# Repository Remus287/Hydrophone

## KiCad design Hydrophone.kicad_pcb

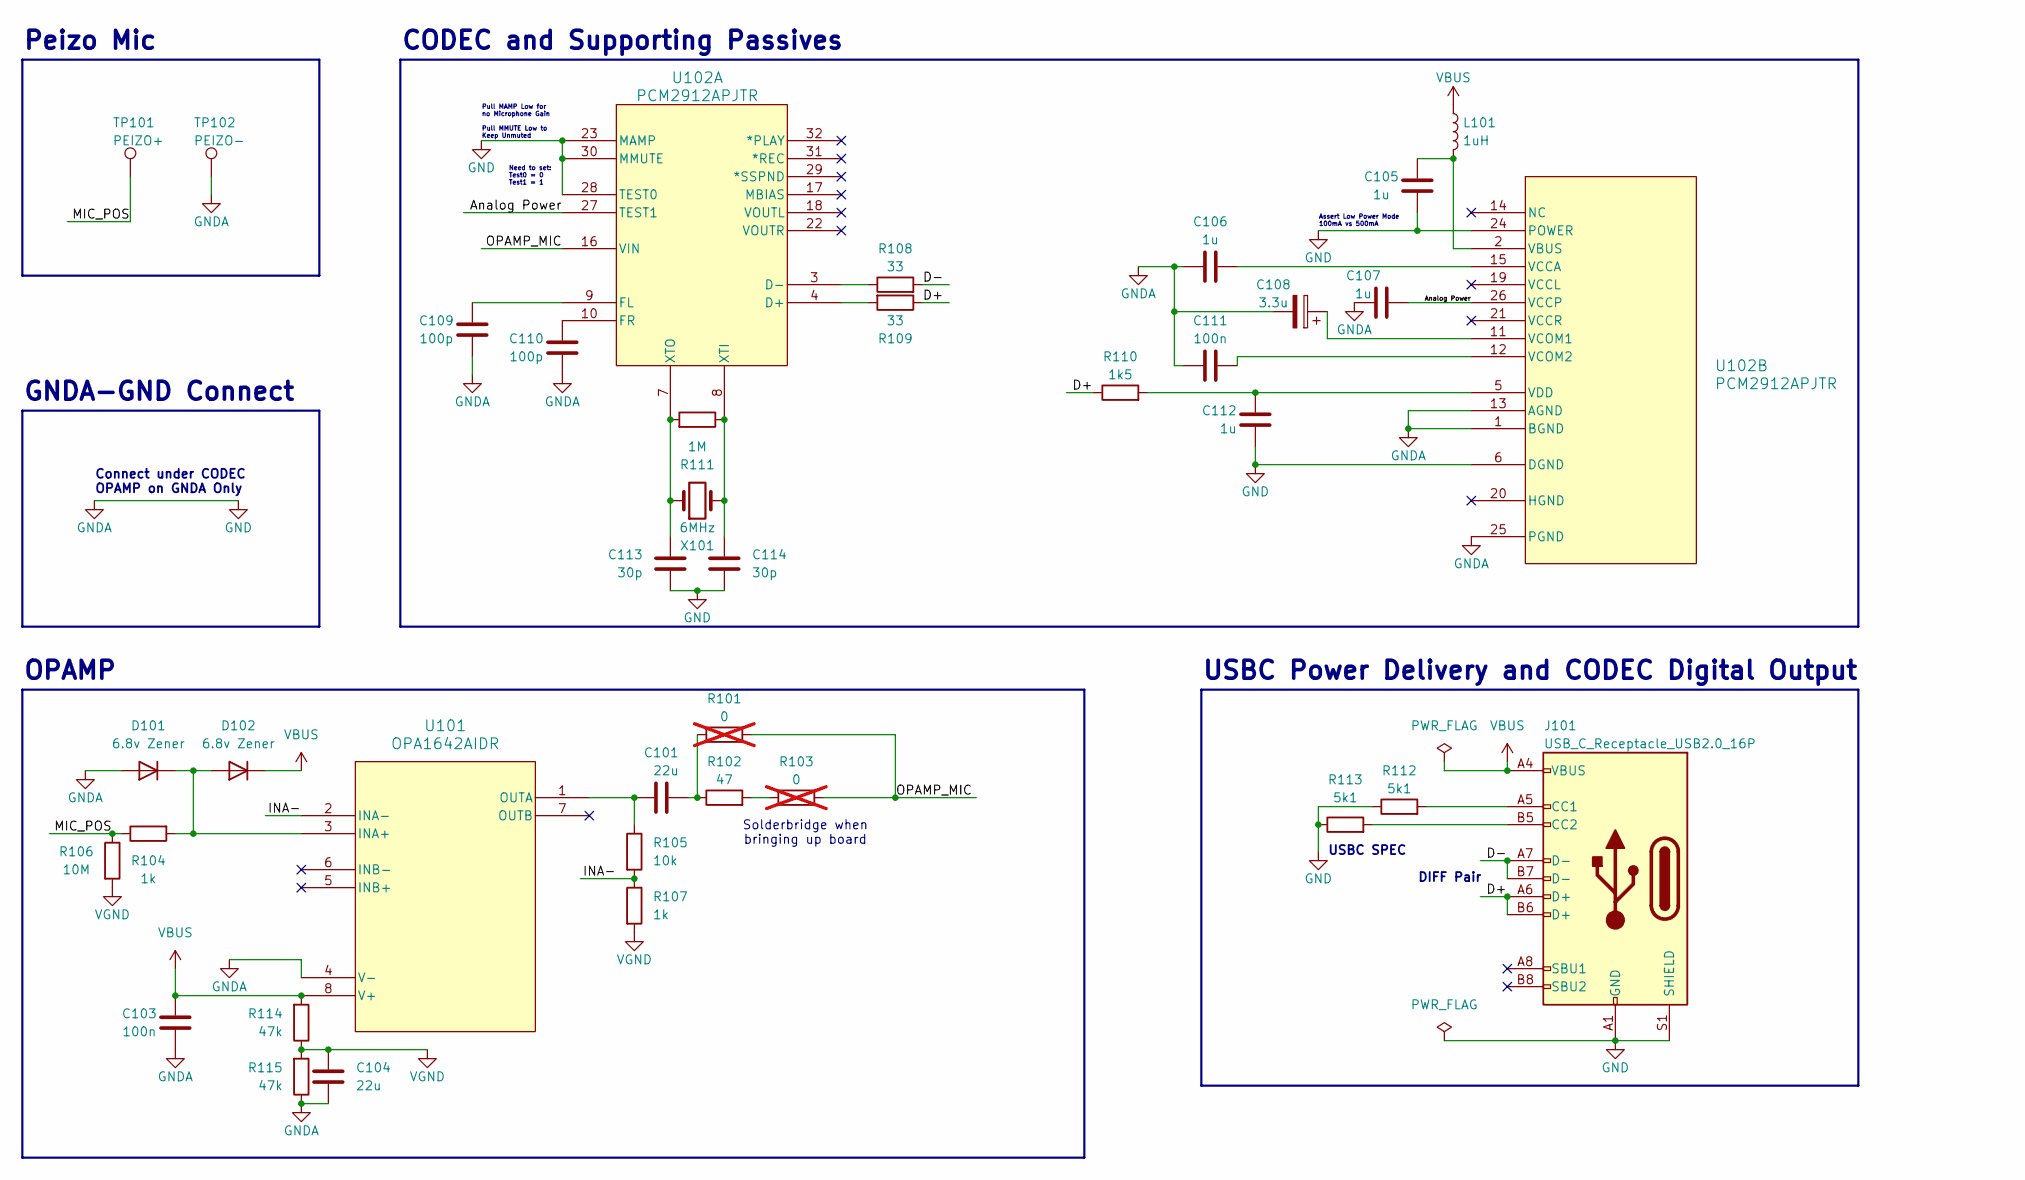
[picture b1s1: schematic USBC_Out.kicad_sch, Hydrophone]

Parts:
C101, C104: 22u; C_0805_2012Metric; Part Number CL21A226MAQNNNE; JLCPCB Part# C45783
C103, C111: 100n; C_0402_1005Metric; Part Number CL05B104KO5NNNC; JLCPCB Part# C1525
C105, C106, C107, C112: 1u; C_0402_1005Metric; Part Number CL05A105KA5NQNC; JLCPCB Part# C52923
C108: 3.3u; CP_EIA-3216-18_Kemet-A; Part Number TAJA335K016RNJ; JLCPCB Part# C7184
C109, C110: 100p; C_0402_1005Metric; Part Number 0402CG101J500NT; JLCPCB Part# C1546
C113, C114: 30p; C_0402_1005Metric; Part Number 0402CG300J500NT; JLCPCB Part# C1570
D101, D102: 6.8v Zener; D_SOD-123; Part Number BZT52C6V8; JLCPCB Part# C2120
J101: USB_C_Receptacle_USB2.0_16P; USB_C_Receptacle_G-Switch_GT-USB-7025; Part Number GT-USB-7025; JLCPCB Part# C963213
L101: 1uH; L_1210_3225Metric; Part Number NLV32T-1R0J-PF; JLCPCB Part# C22202
R101, R103: 0; R_0603_1608Metric; not fitted
R102: 47; R_0805_2012Metric; Part Number 1206W4F1002T5E; JLCPCB Part# C17902
R104, R107: 1k; C_0402_1005Metric; Part Number 0402WGF1001TCE; JLCPCB Part# C11702
R105: 10k; R_1206_3216Metric; Part Number 1206W4F1002T5E; JLCPCB Part# C17902
R106: 10M; R_0402_1005Metric; Part Number 0402WGF1005TCE; JLCPCB Part# C26082
R108, R109: 33; R_0402_1005Metric; Part Number 0402WGF330JTCE; JLCPCB Part# C25105
R110: 1k5; R_0402_1005Metric; Part Number 0402WGJ0152TCE; JLCPCB Part# C25930
R111: 1M; R_0402_1005Metric; Part Number 0402WGF1004TCE; JLCPCB Part# C26083
R112, R113: 5k1; R_0402_1005Metric; Part Number 0402WGF5101TCE; JLCPCB Part# C25905
R114, R115: 47k; R_0402_1005Metric; Part Number 0402WGF4702TCE; JLCPCB Part# C25792
TP101: PEIZO+; TestPoint_Pad_D1.0mm; Part Number ---
TP102: PEIZO-; TestPoint_Pad_D1.0mm; Part Number ---
U101: OPA1642AIDR; D8; Part Number OPA1642AIDR; JLCPCB Part# C67640
U102: PCM2912APJTR; PJT32; Part Number PCM2912APJTR; JLCPCB Part# C475497
X101: 6MHz; Crystal_SMD_HC49-SD; Part Number H6OEL89CSC-SUGYLC-6M; JLCPCB Part# C7528811

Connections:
/USBC_Out/Analog Power: C107.1, U102.26 (VCCP), U102.27 (TEST1)
/USBC_Out/D+: J101.A6 (D+), J101.B6 (D+), R109.1, R110.1
/USBC_Out/D-: J101.A7 (D-), J101.B7 (D-), R108.2
/USBC_Out/INA-: R105.2, R107.1, U101.2 (INA-)
/USBC_Out/MIC_POS: R104.1, R106.1, TP101.1
/USBC_Out/OPAMP_MIC: R101.2, R103.2, U102.16 (VIN)
GND: C103.2, C104.2, C105.2, C106.2, C107.2, C108.2, C109.2, C110.2, C111.2, C112.1, C113.2, C114.2, D101.2 (A), J101.A1 (GND), J101.A12 (GND), J101.B1 (GND), J101.B12 (GND), J101.S1 (SHIELD), R112.1, R113.1, R115.1, TP102.1, U101.4 (V-), U102.1 (BGND), U102.6 (DGND), U102.13 (AGND), U102.23 (MAMP), U102.24 (POWER), U102.25 (PGND), U102.28 (TEST0), U102.30 (MMUTE)
unnamed: C101.1, R101.1, R102.1
unnamed: D101.1 (K), D102.2 (A), R104.2, U101.3 (INA+)
unnamed: J101.A5 (CC1), R112.2
unnamed: J101.B5 (CC2), R113.2
unnamed: R102.2, R103.1
unnamed: C101.2, R105.1, U101.1 (OUTA)
unnamed: R109.2, U102.4 (D+)
unnamed: R108.1, U102.3 (D-)
unnamed: C109.1, U102.9 (FL)
unnamed: C110.1, U102.10 (FR)
unnamed: C114.1, R111.1, U102.8 (XTI), X101.2
unnamed: C113.1, R111.2, U102.7 (XTO), X101.1
unnamed: C105.1, L101.2, U102.2 (VBUS)
unnamed: C106.1, U102.15 (VCCA)
unnamed: C108.1, U102.11 (VCOM1)
unnamed: C111.1, U102.12 (VCOM2)
unnamed: C112.2, R110.2, U102.5 (VDD)
VBUS: C103.1, D102.1 (K), J101.A4 (VBUS), J101.A9 (VBUS), J101.B4 (VBUS), J101.B9 (VBUS), L101.1, R114.2, U101.8 (V+)
VGND: C104.1, R106.2, R107.2, R114.1, R115.2

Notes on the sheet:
DIFF Pair
Need to set: Test0 = 0 Test1 = 1
USBC Power Delivery and CODEC Digital Output
Assert Low Power Mode 100mA vs 500mA
USBC SPEC
CODEC and Supporting Passives
Connect under CODEC OPAMP on GNDA Only
Solderbridge when bringing up board
Peizo Mic
Pull MAMP Low for no Microphone Gain Pull MMUTE Low to Keep Unmuted
OPAMP
GNDA-GND Connect

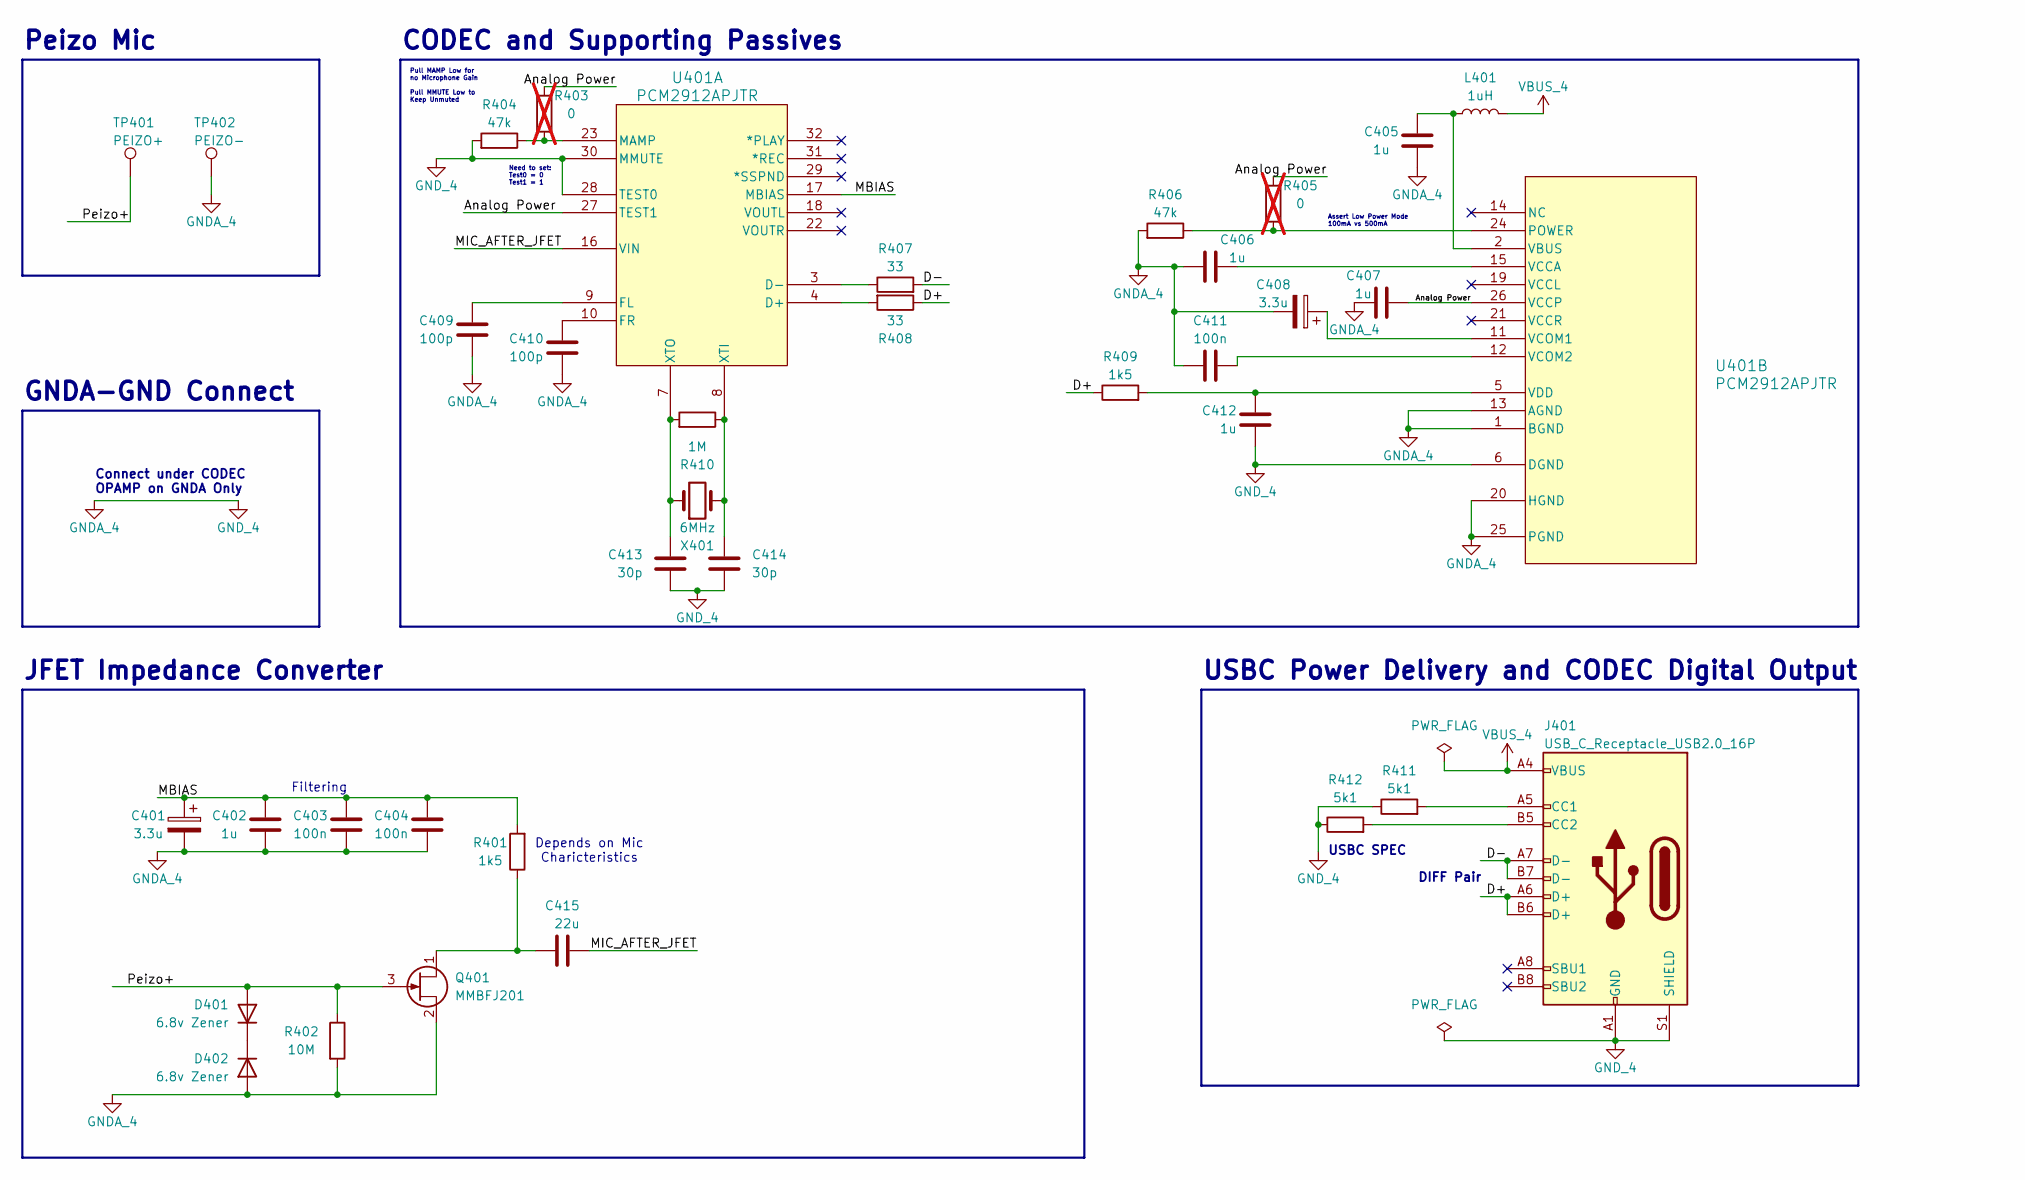
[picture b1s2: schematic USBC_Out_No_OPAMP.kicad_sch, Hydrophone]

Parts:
C401, C408: 3.3u; CP_EIA-3216-18_Kemet-A; Part Number TAJA335K016RNJ; JLCPCB Part# C7184
C402, C405, C406, C407, C412: 1u; C_0402_1005Metric; Part Number CL05A105KA5NQNC; JLCPCB Part# C52923
C403, C404, C411: 100n; C_0402_1005Metric; Part Number CL05B104KO5NNNC; JLCPCB Part# C1525
C409, C410: 100p; C_0402_1005Metric; Part Number 0402CG101J500NT; JLCPCB Part# C1546
C413, C414: 30p; C_0402_1005Metric; Part Number 0402CG300J500NT; JLCPCB Part# C1570
C415: 22u; C_0805_2012Metric; Part Number CL21A226MAQNNNE; JLCPCB Part# C45783
D401, D402: 6.8v Zener; D_SOD-123; Part Number BZT52C6V8; JLCPCB Part# C2120
J401: USB_C_Receptacle_USB2.0_16P; USB_C_Receptacle_G-Switch_GT-USB-7025; Part Number GT-USB-7025; JLCPCB Part# C963213
L401: 1uH; L_1210_3225Metric; Part Number NLV32T-1R0J-PF; JLCPCB Part# C22202
Q401: MMBFJ201; SOT-23; Part Number MMBFJ201; JLCPCB Part# C891687
R401, R409: 1k5; R_0402_1005Metric; Part Number 0402WGJ0152TCE; JLCPCB Part# C25930
R402: 10M; R_0402_1005Metric; Part Number 0402WGF1005TCE; JLCPCB Part# C26082
R403, R405: 0; R_0603_1608Metric; not fitted
R404, R406: 47k; R_0402_1005Metric; Part Number 0402WGF4702TCE; JLCPCB Part# C25792
R407, R408: 33; R_0402_1005Metric; Part Number 0402WGF330JTCE; JLCPCB Part# C25105
R410: 1M; R_0402_1005Metric; Part Number 0402WGF1004TCE; JLCPCB Part# C26083
R411, R412: 5k1; R_0402_1005Metric; Part Number 0402WGF5101TCE; JLCPCB Part# C25905
TP401: PEIZO+; TestPoint_Pad_D1.0mm; Part Number ---
TP402: PEIZO-; TestPoint_Pad_D1.0mm; Part Number ---
U401: PCM2912APJTR; PJT32; Part Number PCM2912APJTR; JLCPCB Part# C475497
X401: 6MHz; Crystal_SMD_HC49-SD; Part Number H6OEL89CSC-SUGYLC-6M; JLCPCB Part# C7528811

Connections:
/USBC_Out_No_OPAMP/Analog Power: C407.1, R403.2, R405.2, U401.26 (VCCP), U401.27 (TEST1)
/USBC_Out_No_OPAMP/D+: J401.A6 (D+), J401.B6 (D+), R408.1, R409.1
/USBC_Out_No_OPAMP/D-: J401.A7 (D-), J401.B7 (D-), R407.2
/USBC_Out_No_OPAMP/MBIAS: C401.1, C402.2, C403.2, C404.2, R401.2, U401.17 (MBIAS)
/USBC_Out_No_OPAMP/MIC_AFTER_JFET: C415.1, U401.16 (VIN)
/USBC_Out_No_OPAMP/Peizo+: D401.2 (A), Q401.3 (G), R402.1, TP401.1
GNDA_4: C401.2, C402.1, C403.1, C404.1, C405.2, C406.2, C407.2, C408.2, C409.2, C410.2, C411.2, C412.1, C413.2, C414.2, D402.2 (A), J401.A1 (GND), J401.A12 (GND), J401.B1 (GND), J401.B12 (GND), J401.S1 (SHIELD), Q401.2 (S), R402.2, R404.2, R406.2, R411.1, R412.1, TP402.1, U401.1 (BGND), U401.6 (DGND), U401.13 (AGND), U401.20 (HGND), U401.25 (PGND), U401.28 (TEST0), U401.30 (MMUTE)
unnamed: D401.1 (K), D402.1 (K)
unnamed: J401.A5 (CC1), R411.2
unnamed: J401.B5 (CC2), R412.2
unnamed: C415.2, Q401.1 (D), R401.1
unnamed: R408.2, U401.4 (D+)
unnamed: R407.1, U401.3 (D-)
unnamed: C409.1, U401.9 (FL)
unnamed: C410.1, U401.10 (FR)
unnamed: R403.1, R404.1, U401.23 (MAMP)
unnamed: C414.1, R410.1, U401.8 (XTI), X401.2
unnamed: C413.1, R410.2, U401.7 (XTO), X401.1
unnamed: R405.1, R406.1, U401.24 (POWER)
unnamed: C405.1, L401.2, U401.2 (VBUS)
unnamed: C406.1, U401.15 (VCCA)
unnamed: C408.1, U401.11 (VCOM1)
unnamed: C411.1, U401.12 (VCOM2)
unnamed: C412.2, R409.2, U401.5 (VDD)
VBUS_4: J401.A4 (VBUS), J401.A9 (VBUS), J401.B4 (VBUS), J401.B9 (VBUS), L401.1

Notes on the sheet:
Assert Low Power Mode 100mA vs 500mA
DIFF Pair
Peizo Mic
CODEC and Supporting Passives
JFET Impedance Converter
Need to set: Test0 = 0 Test1 = 1
USBC SPEC
GNDA-GND Connect
USBC Power Delivery and CODEC Digital Output
Filtering
Connect under CODEC OPAMP on GNDA Only
Depends on Mic Charicteristics
Pull MAMP Low for no Microphone Gain Pull MMUTE Low to Keep Unmuted

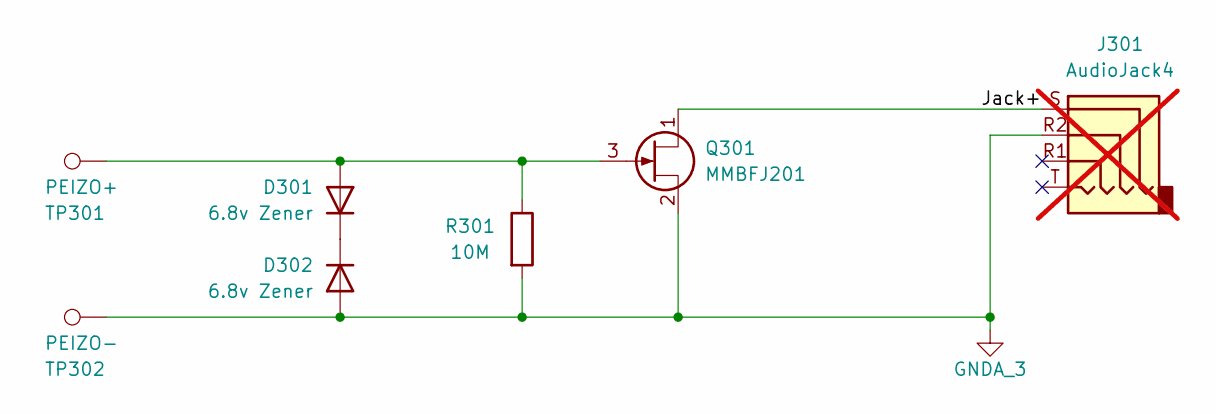
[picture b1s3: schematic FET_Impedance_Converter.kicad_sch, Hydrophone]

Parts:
D301, D302: 6.8v Zener; D_SOD-123; Part Number BZT52C6V8; JLCPCB Part# C2120
J301: AudioJack4; Jack_3.5mm_PJ320D_Horizontal; not fitted
Q301: MMBFJ201; SOT-23; Part Number MMBFJ201; JLCPCB Part# C891687
R301: 10M; R_0402_1005Metric; Part Number 0402WGF1005TCE; JLCPCB Part# C26082
TP301: PEIZO+; TestPoint_Pad_D1.0mm; Part Number ---
TP302: PEIZO-; TestPoint_Pad_D1.0mm; Part Number ---

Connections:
/FET_Impedance_Converter/Jack+: J301.S, Q301.1 (D)
GNDA_3: D302.2 (A), J301.R2, Q301.2 (S), R301.2, TP302.1
unnamed: D301.2 (A), Q301.3 (G), R301.1, TP301.1
unnamed: D301.1 (K), D302.1 (K)

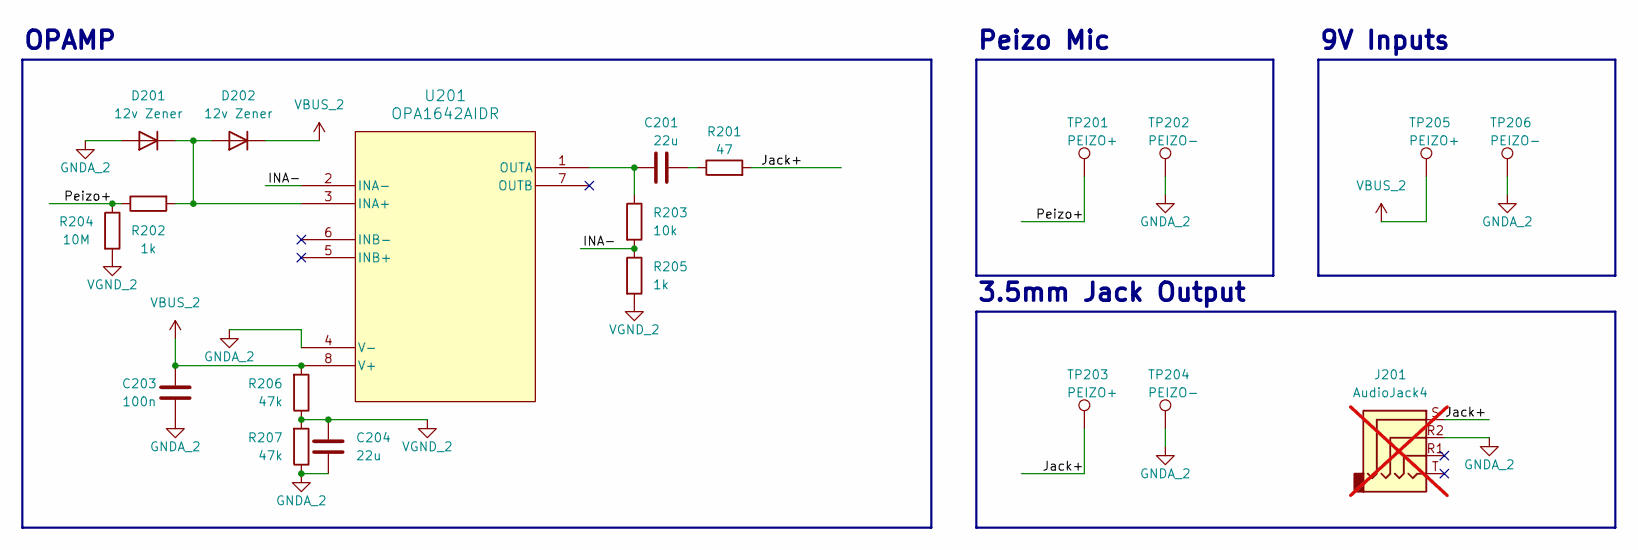
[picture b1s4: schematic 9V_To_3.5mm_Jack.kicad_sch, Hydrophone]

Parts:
C201, C204: 22u; C_0805_2012Metric; Part Number CL21A226MAQNNNE; JLCPCB Part# C45783
C203: 100n; C_0402_1005Metric; Part Number CL05B104KO5NNNC; JLCPCB Part# C1525
D201, D202: 12v Zener; D_SOD-123; Part Number BZT52C12; JLCPCB Part# C43491
J201: AudioJack4; Jack_3.5mm_PJ320D_Horizontal; not fitted
R201: 47; R_0805_2012Metric; Part Number 1206W4F1002T5E; JLCPCB Part# C17902
R202, R205: 1k; C_0402_1005Metric; Part Number 0402WGF1001TCE; JLCPCB Part# C11702
R203: 10k; R_1206_3216Metric; Part Number 1206W4F1002T5E; JLCPCB Part# C17902
R204: 10M; R_0402_1005Metric; Part Number 0402WGF1005TCE; JLCPCB Part# C26082
R206, R207: 47k; R_0402_1005Metric; Part Number 0402WGF4702TCE; JLCPCB Part# C25792
TP201, TP203, TP205: PEIZO+; TestPoint_Pad_D1.0mm; Part Number ---
TP202, TP204, TP206: PEIZO-; TestPoint_Pad_D1.0mm; Part Number ---
U201: OPA1642AIDR; D8; Part Number OPA1642AIDR; JLCPCB Part# C67640

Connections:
/9V_To_3.5mm_Jack/INA-: R203.2, R205.1, U201.2 (INA-)
/9V_To_3.5mm_Jack/Jack+: J201.S, R201.2, TP203.1
/9V_To_3.5mm_Jack/Peizo+: R202.1, R204.1, TP201.1
GNDA_2: C203.2, C204.2, D201.2 (A), J201.R2, R207.1, TP202.1, TP204.1, TP206.1, U201.4 (V-)
unnamed: C201.1, R201.1
unnamed: D201.1 (K), D202.2 (A), R202.2, U201.3 (INA+)
unnamed: C201.2, R203.1, U201.1 (OUTA)
VBUS_2: C203.1, D202.1 (K), R206.2, TP205.1, U201.8 (V+)
VGND_2: C204.1, R204.2, R205.2, R206.1, R207.2

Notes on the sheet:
Peizo Mic
OPAMP
3.5mm Jack Output
9V Inputs

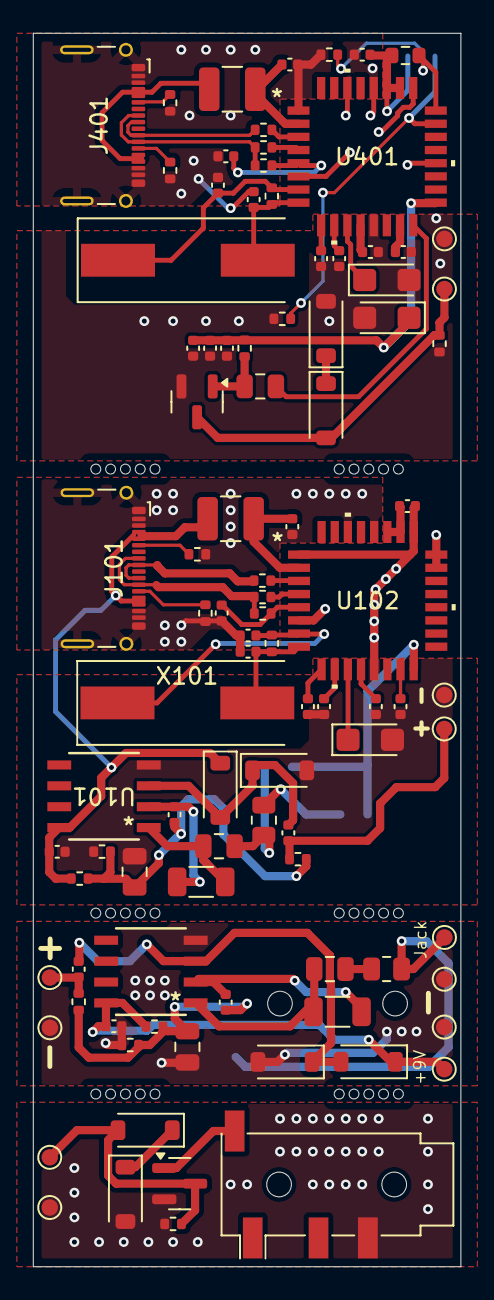
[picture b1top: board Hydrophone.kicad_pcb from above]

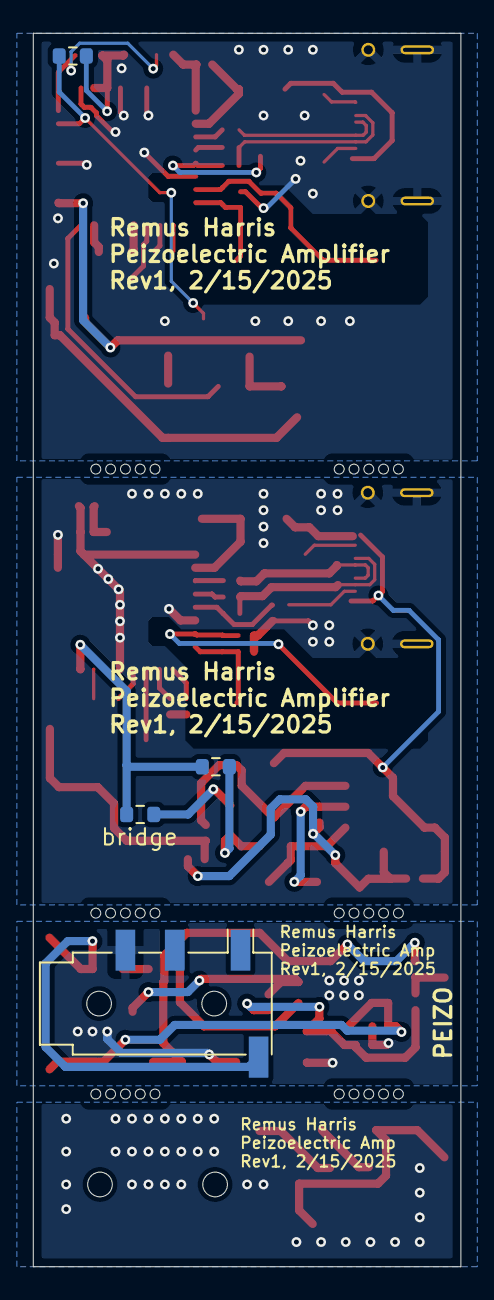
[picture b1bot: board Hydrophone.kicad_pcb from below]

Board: 2 copper layers, 26.0 x 75.0 mm, 100 parts (4 on the bottom side), 64 nets.

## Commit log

2025-02-16 added dual channel op-amp lib file
2025-02-16 added CODEC lib file
2025-02-16 finished digital pcb version
2025-02-17 repo as manufactured
2025-02-19 fixed BOM to correct part number for 47ohm 0805 resistor. New file sent to JLCPCB for manufacturing
2025-03-07 added top sheet drawing to schematic
